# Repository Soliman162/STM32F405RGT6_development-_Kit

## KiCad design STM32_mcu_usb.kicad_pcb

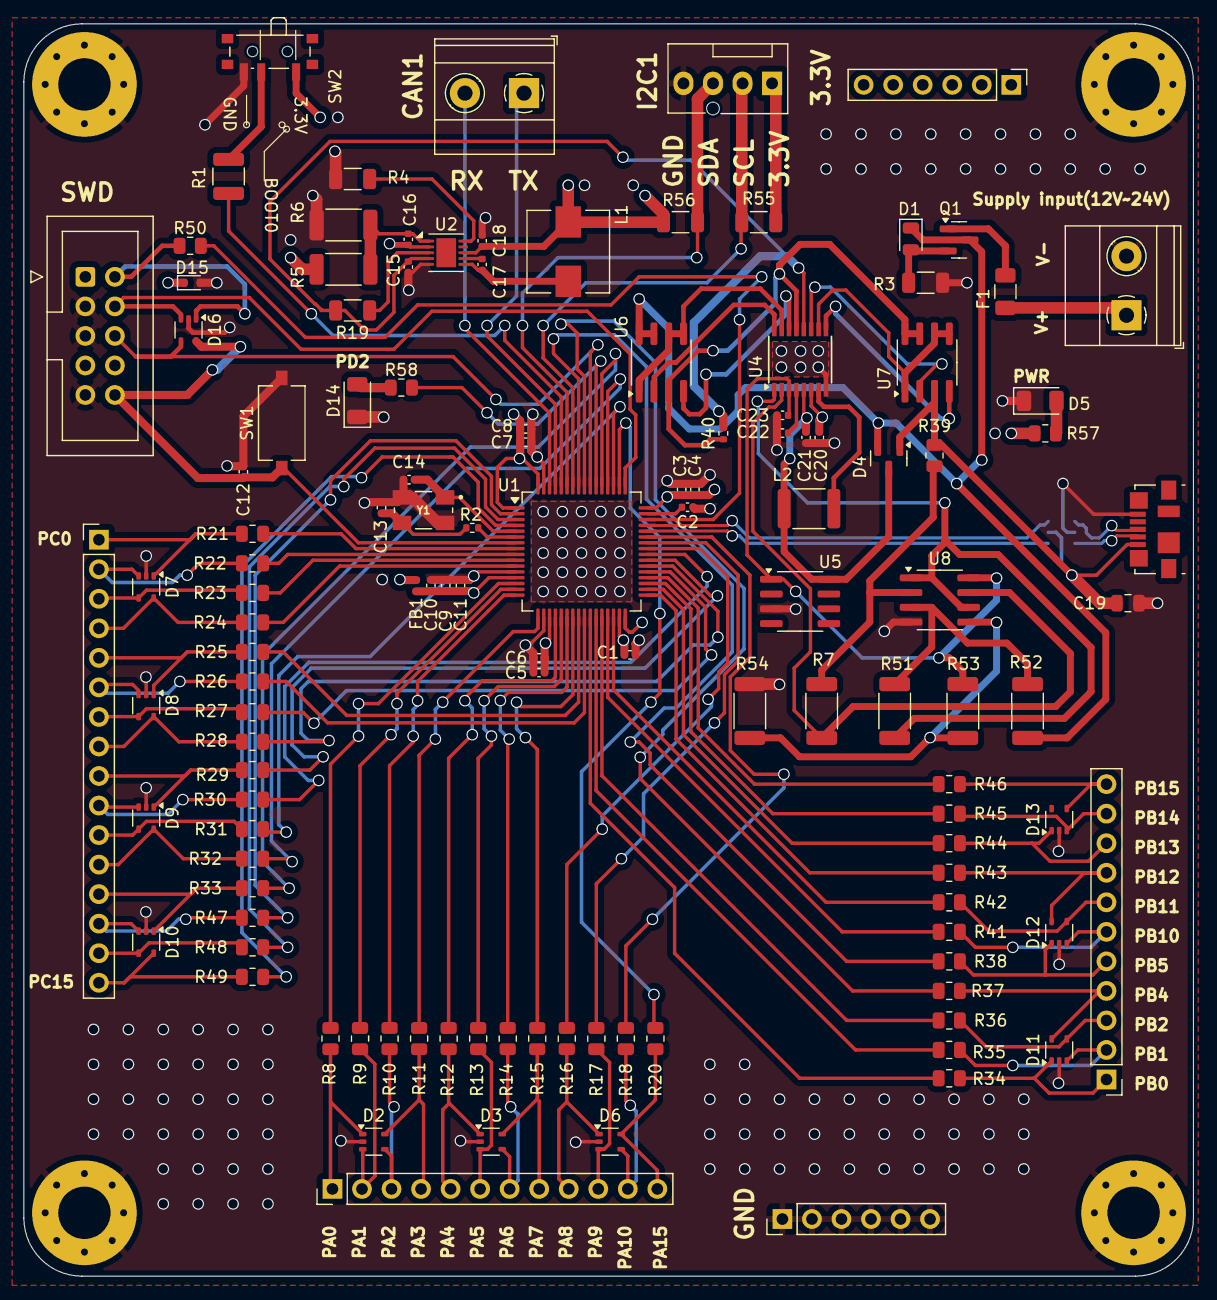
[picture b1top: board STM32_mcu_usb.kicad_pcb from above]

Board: 4 copper layers, 100.6 x 107.7 mm, 127 parts (1 on the bottom side), 132 nets.

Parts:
C1, C2, C3, C4, C5, C6, C7, C9, C10, C12: 100nF; C_0402_1005Metric
C8: 4C7uF; C_0402_1005Metric
C11: 1uF; C_0402_1005Metric
C13, C14: 2.5pF; C_0402_1005Metric
C15: 4.7uF; C_0402_1005Metric
C16: 15pF; C_0402_1005Metric
C17: 0.47uF; C_0402_1005Metric
C18: 22uF; C_0402_1005Metric
C19: 100nF; C_0805_2012Metric
C20, C21, C23: 1F; C_0402_1005Metric
C22: 4700pF; C_0402_1005Metric
D1: 12V; D_0805_2012Metric
D2, D3, D6, D7, D8, D9, D10, D11, D12, D13, D16: SP0504BAJT; SOT-353_SC-70-5
D4: MMBD2837LT1G; SOT-23
D5: Red; LED_1206_3216Metric
D14: Blue; LED_1206_3216Metric
D15: SMLVT3V3; D_SOD-523
F1: 500mA; Fuse_1206_3216Metric
FB1: FerriteBead; L_0402_1005Metric
H1, H2, H3, H4: MountingHole_Pad; MountingHole_4.5mm_Pad_Via
J1: CAN1; TerminalBlock_Phoenix_MKDS-1,5-2-5.08_1x02_P5.08mm_Horizont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
J2: I2C1_conn; FanPinHeader_1x04_P2.54mm_Vertical
J3: PortC_conn; PinHeader_1x16_P2.54mm_Vertical
J5: PORTA_Conn; PinHeader_1x12_P2.54mm_Vertical
J6: 3.3V_Conn; PinHeader_1x06_P2.54mm_Vertical
J7: SWD; IDC-Header_2x05_P2.54mm_Vertical
J8: Power_supply; TerminalBlock_Phoenix_MKDS-1,5-2-5.08_1x02_P5.08mm_Horizont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
J9: GND_Conn; PinHeader_1x06_P2.54mm_Vertical
J10: USB_B_Micro; USB_Micro-B_Molex_47346-0001
J11: PortB_conn; PinHeader_1x11_P2.54mm_Vertical
L1: 10uH; L_Wuerth_HCI-7030
L2: 1mH; L_1812_4532Metric
Q1: PMOS; SOT-23
R1: 10K; R_1210_3225Metric
R2: 1M; R_0402_1005Metric
R3: 100K; R_1206_3216Metric
R4: 73.2K; R_1206_3216Metric
R5, R7, R51, R53, R54: 1M; R_2010_5025Metric
R6: 576K; R_2010_5025Metric
R8, R9, R10, R11, R12, R13, R14, R15, R16, R17, R18, R20, R21, R22, R23, R24, R25, R26, R27, R28, R29, R30, R31, R32, R33, R34, R35, R36, R37, R38, R41, R42, R43, R44, R45, R46, R47, R48, R49, R50: 150R; R_0805_2012Metric
R19: 73.2k; R_1206_3216Metric
R39: 10K; R_0805_2012Metric
R40: 33m; R_0402_1005Metric
R52: 10K; R_2010_5025Metric
R55, R56: 4R7K; R_1206_3216Metric
R57, R58: 1k5; R_0805_2012Metric
SW1: SW_Push; SW_Tactile_SPST_NO_Straight_CK_PTS636Sx25SMTRLFS
SW2: SW_Push_SPDT; SW_SPDT_PCM12
U1: STM32F405RGT6; LQFP-64_10x10mm_P0.5mm
U2: LT3973-3.3V; DFN-10-1EP_3x3mm_P0.5mm_EP1.7x2.5mm
U3: USBLC6-2SC6; SOT-23-6
U4: LTC1473CGN#PBF; SSOP-16_3.9x4.9mm_P0.635mm
U5: LT1121ACS8-5#PBF; SOIC-8_3.9x4.9mm_P1.27mm
U6, U7: SI9926CDY-T1-E3; SOIC-8_3.9x4.9mm_P1.27mm
U8: LT1490ACMS8#PBF; SOIC-8_3.9x4.9mm_P1.27mm
Y1: ECS-200-10-30B-CKM-TR; XTAL_ECS-200-10-30B-CKM-TR

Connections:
+3.3V: C3.1, C4.1, C5.1, C6.1, C7.1, C8.1, C16.1, C18.1, D15.1 (K), FB1.1, J2.1, J6.1, J6.2, J6.3, J6.4, J6.5, J6.6, J7.1, L1.2, R5.1, R55.1, R56.1, R57.1, SW2.1 (A), U1.1 (VBAT), U1.19 (VDD), U1.32 (VDD), U1.48 (VDD), U1.64 (VDD), U2.2 (OUT), U2.8 (BD)
+3.3VA: C9.1, C10.1, C11.1, FB1.2, U1.13 (VDDA)
+5V: C19.1, D4.1 (A), J10.1 (VBUS), R39.2, U3.5 (VBUS), U7.3 (S2)
/BOOT0: R1.2, U1.60 (BOOT0)
/CAN1_RX: J1.1, U1.61 (PB8)
/CAN1_TX: J1.2, U1.62 (PB9)
/D+: J10.3 (D+), U3.1 (I/O1)
/D-: J10.2 (D-), U3.3 (I/O2)
/I2C1_SCL: J2.2, R55.2, U1.58 (PB6)
/I2C1_SDA: J2.3, R56.2, U1.59 (PB7)
/INB+_LT: R53.2, R54.1, U8.5 (INB+)
/INB-_LT: R51.2, U4.1 (IN1), U8.1 (OUTA), U8.6 (INB-)
/NRST: C12.1, D16.5 (K), J7.10, SW1.1, U1.7 (NRST)
/OSC_IN: C14.1, U1.5 (PH0), Y1.1 (IN/OUT)
/OSC_OUT: R2.1, U1.6 (PH1)
/PA0: R8.1, U1.14 (PA0)
/PA1: R9.1, U1.15 (PA1)
/PA2: R10.1, U1.16 (PA2)
/PA3: R11.1, U1.17 (PA3)
/PA4: R12.1, U1.20 (PA4)
/PA5: R13.1, U1.21 (PA5)
/PA6: R14.1, U1.22 (PA6)
/PA7: R15.1, U1.23 (PA7)
/PA8: R16.1, U1.41 (PA8)
/PA9: R17.1, U1.42 (PA9)
/PA10: R18.1, U1.43 (PA10)
/PA15: R20.1, U1.50 (PA15)
/PB0: R34.1, U1.26 (PB0)
/PB1: R35.1, U1.27 (PB1)
/PB2: R36.1, U1.28 (PB2)
/PB4: R37.1, U1.56 (PB4)
/PB5: R38.1, U1.57 (PB5)
/PB10: R41.1, U1.29 (PB10)
/PB11: R42.1, U1.30 (PB11)
/PB12: R43.1, U1.33 (PB12)
/PB13: R44.1, U1.34 (PB13)
/PB14: R45.1, U1.35 (PB14)
/PB15: R46.1, U1.36 (PB15)
/PC0: R21.1, U1.8 (PC0)
/PC1: R22.1, U1.9 (PC1)
/PC2: R23.1, U1.10 (PC2)
/PC3: R24.1, U1.11 (PC3)
/PC4: R25.1, U1.24 (PC4)
/PC5: R26.1, U1.25 (PC5)
/PC6: R27.1, U1.37 (PC6)
/PC7: R28.1, U1.38 (PC7)
/PC8: R29.1, U1.39 (PC8)
/PC9: R30.1, U1.40 (PC9)
/PC10: R31.1, U1.51 (PC10)
/PC11: R32.1, U1.52 (PC11)
/PC12: R33.1, U1.53 (PC12)
/PC13: R47.1, U1.2 (PC13)
/PC14: R48.1, U1.3 (PC14)
/PC15: R49.1, U1.4 (PC15)
/Power_OUT: C15.1, R19.1, R40.2, U2.4 (Vin), U4.12 (SENSE-)
/SWCLK: D16.3 (K), J7.4, U1.49 (PA14)
/SWDIO: R50.1, U1.46 (PA13)
/SWO: D16.4 (K), J7.6, U1.55 (PB3)
/Supply_IN: F1.1, J8.1
/Supply_out: D1.1 (K), D4.2 (A), Q1.3 (S), R52.1, U6.7 (D1), U6.8 (D1)
/USB+: U1.45 (PA12), U3.6 (I/O1)
/USB-: U1.44 (PA11), U3.4 (I/O2)
GND: C1.2, C2.2, C3.2, C4.2, C5.2, C6.2, C7.2, C8.2, C9.2, C10.2, C11.2, C12.2, C13.2, C14.2, C15.2, C18.2, C19.2, C20.2, C21.2, C22.2, C23.2, D2.2 (A), D3.2 (A), D5.1 (K), D6.2 (A), D7.2 (A), D8.2 (A), D9.2 (A), D10.2 (A), D11.2 (A), D12.2 (A), D13.2 (A), D14.1 (K), D15.2 (A), D16.2 (A), H1.1, H2.1, H3.1, H4.1, J2.4, J7.3, J7.5, J7.9, J8.2, J9.1, J9.2, J9.3, J9.4, J9.5, J9.6, J10.5 (GND), R3.1, R4.2, R6.2, R54.2, SW1.2, SW2.3 (C), U1.12 (VSSA), U1.18 (VSS), U1.63 (VSS), U2.5 (GND), U3.2 (GND), U4.8 (GND), U5.3 (GND), U8.4 (V-), Y1.2 (GND), Y1.4 (GND)
unnamed: D1.2 (A), Q1.2 (G), R3.2
unnamed: C21.1, D4.3 (K), L2.1, U4.5 (V+), U5.8 (IN)
unnamed: D5.2 (A), R57.2
unnamed: D14.2 (A), R58.2
unnamed: D7.1 (K), J3.1, R21.2
unnamed: D7.3 (K), J3.2, R22.2
unnamed: D7.4 (K), J3.3, R23.2
unnamed: D7.5 (K), J3.4, R24.2
unnamed: D8.1 (K), J3.5, R25.2
unnamed: D8.3 (K), J3.6, R26.2
unnamed: D8.4 (K), J3.7, R27.2
unnamed: D8.5 (K), J3.8, R28.2
unnamed: D9.1 (K), J3.9, R29.2
unnamed: D9.3 (K), J3.10, R30.2
unnamed: D9.4 (K), J3.11, R31.2
unnamed: D9.5 (K), J3.12, R32.2
unnamed: D10.1 (K), J3.13, R33.2
unnamed: D10.3 (K), J3.14, R47.2
unnamed: D10.4 (K), J3.15, R48.2
unnamed: D10.5 (K), J3.16, R49.2
unnamed: D2.1 (K), J5.1, R8.2
unnamed: D2.3 (K), J5.2, R9.2
unnamed: D2.4 (K), J5.3, R10.2
unnamed: D2.5 (K), J5.4, R11.2
unnamed: D3.1 (K), J5.5, R12.2
unnamed: D3.3 (K), J5.6, R13.2
unnamed: D3.4 (K), J5.7, R14.2
unnamed: D3.5 (K), J5.8, R15.2
unnamed: D6.1 (K), J5.9, R16.2
unnamed: D6.3 (K), J5.10, R17.2
unnamed: D6.4 (K), J5.11, R18.2
unnamed: D6.5 (K), J5.12, R20.2
unnamed: D16.1 (K), J7.2, R50.2
unnamed: D11.1 (K), J11.1, R34.2
unnamed: D11.3 (K), J11.2, R35.2
unnamed: D11.4 (K), J11.3, R36.2
unnamed: D11.5 (K), J11.4, R37.2
unnamed: D12.1 (K), J11.5, R38.2
unnamed: D12.3 (K), J11.6, R41.2
unnamed: D12.4 (K), J11.7, R42.2
unnamed: D12.5 (K), J11.8, R43.2
unnamed: D13.1 (K), J11.9, R44.2
unnamed: D13.3 (K), J11.10, R45.2
unnamed: D13.4 (K), J11.11, R46.2
unnamed: F1.2, Q1.1 (D)
unnamed: R1.1, SW2.2 (B)
unnamed: R58.1, U1.54 (PD2)
unnamed: C1.1, U1.31 (VCAP_1)
unnamed: C2.1, U1.47 (VCAP_2)
unnamed: C17.1, U2.7 (Boost)
unnamed: R19.2, U2.3 (EN/UVLO)
unnamed: C16.2, R5.2, R6.1, U2.1 (FB)
unnamed: R4.1, U2.10 (RT)
unnamed: C17.2, L1.1, U2.6 (SW)
unnamed: C23.1, R53.1, U4.3 (DIODE), U5.1 (OUT), U8.8 (V+)
unnamed: U4.16 (GA1), U6.2 (G1)
unnamed: U4.11 (GA2), U7.2 (G1)
unnamed: U4.14 (GB1), U6.4 (G2)
unnamed: U4.9 (GB2), U7.4 (G2)
unnamed: R7.1, U4.2 (IN2), U8.7 (OUTB)
unnamed: U4.15 (SAB1), U6.1 (S1), U6.5 (D2), U6.6 (D2)
unnamed: U4.10 (SAB2), U7.1 (S1), U7.5 (D2), U7.6 (D2)
unnamed: R40.1, U4.13 (SENSE+), U6.3 (S2), U7.7 (D1), U7.8 (D1)
unnamed: L2.2, U4.7 (SW)
unnamed: C22.1, U4.4 (TIMER)
unnamed: C20.1, U4.6 (VGG)
unnamed: R51.1, R52.2, U8.3 (INA+)
unnamed: R7.2, R39.1, U8.2 (INA-)
unnamed: C13.1, R2.2, Y1.3 (OUT/IN)

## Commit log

2024-09-16 add png
